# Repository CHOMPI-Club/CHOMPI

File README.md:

# CHOMPI — Open Source

**CHOMPI** is a quirky chromatic sampler and tape-music instrument by
[CHOMPI Club](https://www.chompiclub.com).

This repo contains all of the production files, both hardware and firmware, that make up the CHOMPI Sampler.

---

## What's here

| | |
|---|---|
| [**Firmware — Start Here**](firmware/README.md) | Quick instructions for setting up your development environment, building the firmware, and loading it onto your CHOMPI. |
| [`firmware/chompi-wave`](firmware/chompi-wave/) | **WAVE 1.0**, a wavetable synth firmware that doubles as a starting point for anyone writing their own firmware. |
| [`firmware/chompi-tempo`](firmware/chompi-tempo/) | **TEMPO 1.0**, a pattern generator firmware — the counterpart to TAPE. |
| [`firmware/chompi-tape`](firmware/chompi-tape/) | **TAPE 2.0**, the sampler firmware every CHOMPI ships with. |
| [`firmware/chompi-bootloader-v6.4-beta`](firmware/chompi-bootloader-v6.4-beta/) | This bootloader never shipped on units, but was created to improve stability of the Daisy Seed's integration with CHOMPI's hardware as well as repair edge-case issues related to bugs inherited from older versions of the Electrosmith bootloader.  |
| [`firmware/card-profiles`](firmware/card-profiles/) | The factory microSD card contents for TAPE, TEMPO and WAVE — firmware, samples and settings. |
| [`hardware/hardware-pcb`](hardware/hardware-pcb/) | Schematic, BOM, EAGLE PCB files, and the full fabrication package. |
| [`hardware/hardware-enclosure`](hardware/hardware-enclosure/) | The six pcb panel enclosure files, as well as laser cutting files for diy panels. |

Each folder contains its own README, so check those out for more details.

## What's not here

**The panel artwork.** The graphic set and CHOMPI logos have all been removed for copyright purposes. If you choose to create your own hardware, we ask that you name it something else to avoid trademark infringement.

## Support Guidelines

This is a discontinuation open-source release. As such, this repo is intended to be a permanent source for files and documentation, and will likely not be receiving updates in the future. If you wish to customize your own project, we recommend cloning this repo into your own GitHub.

## Community

Even though this version of CHOMPI is now discontinued, the CLUB is expanding. If you want to discuss this project, share your creations, see what other users have made on their CHOMPI, feel free to check out the CHOMPI Open Source channel on the Chase Bliss Discord.

## License

Everything here is **MIT** — see [`LICENSE`](LICENSE). [`THIRD_PARTY.md`](THIRD_PARTY.md) lists
the work this builds on and the notices that come with it. The CHOMPI name, logo and artwork are
not covered by the license — see [`TRADEMARKS.md`](TRADEMARKS.md).

## HAPPY CHOMPIN'

---

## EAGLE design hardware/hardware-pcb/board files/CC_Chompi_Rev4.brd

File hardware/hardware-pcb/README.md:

# CHOMPI — Hardware, Revision 4

The production files for **CHOMPI**'s two internal circuit boards: schematic, BOM, EAGLE
PCB files, and the full fabrication package that was used by Electro-Smith for manufacturing.

---

## What this is

Two boards, built around the Daisy Seed, laid out as one v-scored panel:

- **Bottom board** — the Daisy Seed2 DFM, a PCM3060 second codec, the MP2722 charger for the
  LiPo battery, USB-C, microSD, MEMS microphone, five 3.5 mm jacks, etc.
- **Top board** — 28 Kailh hot-swap key sockets read through CD4021 shift registers, six
  encoders, 35 addressable RGB LEDs, etc.

1 oz copper, ENIG, black soldermask, SMT assembly on both sides.

## What's in the folder

```
CHOMPI_Rev4_Schematic.pdf     the schematic
CHOMPI_Rev4_BOM.csv           assembly parts list: quantity, manufacturer part number, value,
                              package, designators, etc.
board files/                  the EAGLE project files
  CC_Chompi_Rev4.sch            schematic
  CC_Chompi_Rev4.brd            both boards in one .brd layout
  CC_Chompi_Rev4_1X1.brd        the same boards on the fabrication panel, with rails
fabrication/                  mfg package ordered September 2023
  CC_Chompi_Rev4_1X1.zip        gerbers, drill file, v-score file
  CC_Chompi_Rev4-smd_cleaned_centroid.txt   pick-and-place positions
  CC_Chompi_Rev4_1X1_ordering.txt           the fabrication parameters
```

## What's not here

- **The enclosure.** The six enclosure panels have their own folder.
- **Parts list.** The BOM names a manufacturer part number for every placed part.
- **The rest of the instrument.** The Daisy Seed2 DFM is a separate module; the battery,
  keycaps, knobs and cables aren't included in these files, most of which were custom parts orders.

If you build your own hardware from these files, we ask that you name it something else to
avoid trademark infringement.

## Support Guidelines

This is a discontinuation open-source release. As such, this repo is intended to be a permanent
source for files and documentation, and will likely not be receiving updates in the future. If you wish
to customize your own project, we recommend cloning this repo into your own GitHub.

## Community

Even though this version of CHOMPI is now discontinued, the CLUB is expanding. If you want to
discuss this project, share your creations, see what other users have made on their CHOMPI, feel
free to check out the CHOMPI Open Source channel on the Chase Bliss Discord.

## License

MIT — see [`LICENSE`](../../LICENSE) at the root of this repo. [`THIRD_PARTY.md`](../../THIRD_PARTY.md)
lists the work this builds on. The CHOMPI name and marks are not covered by the license — see
[`TRADEMARKS.md`](../../TRADEMARKS.md).

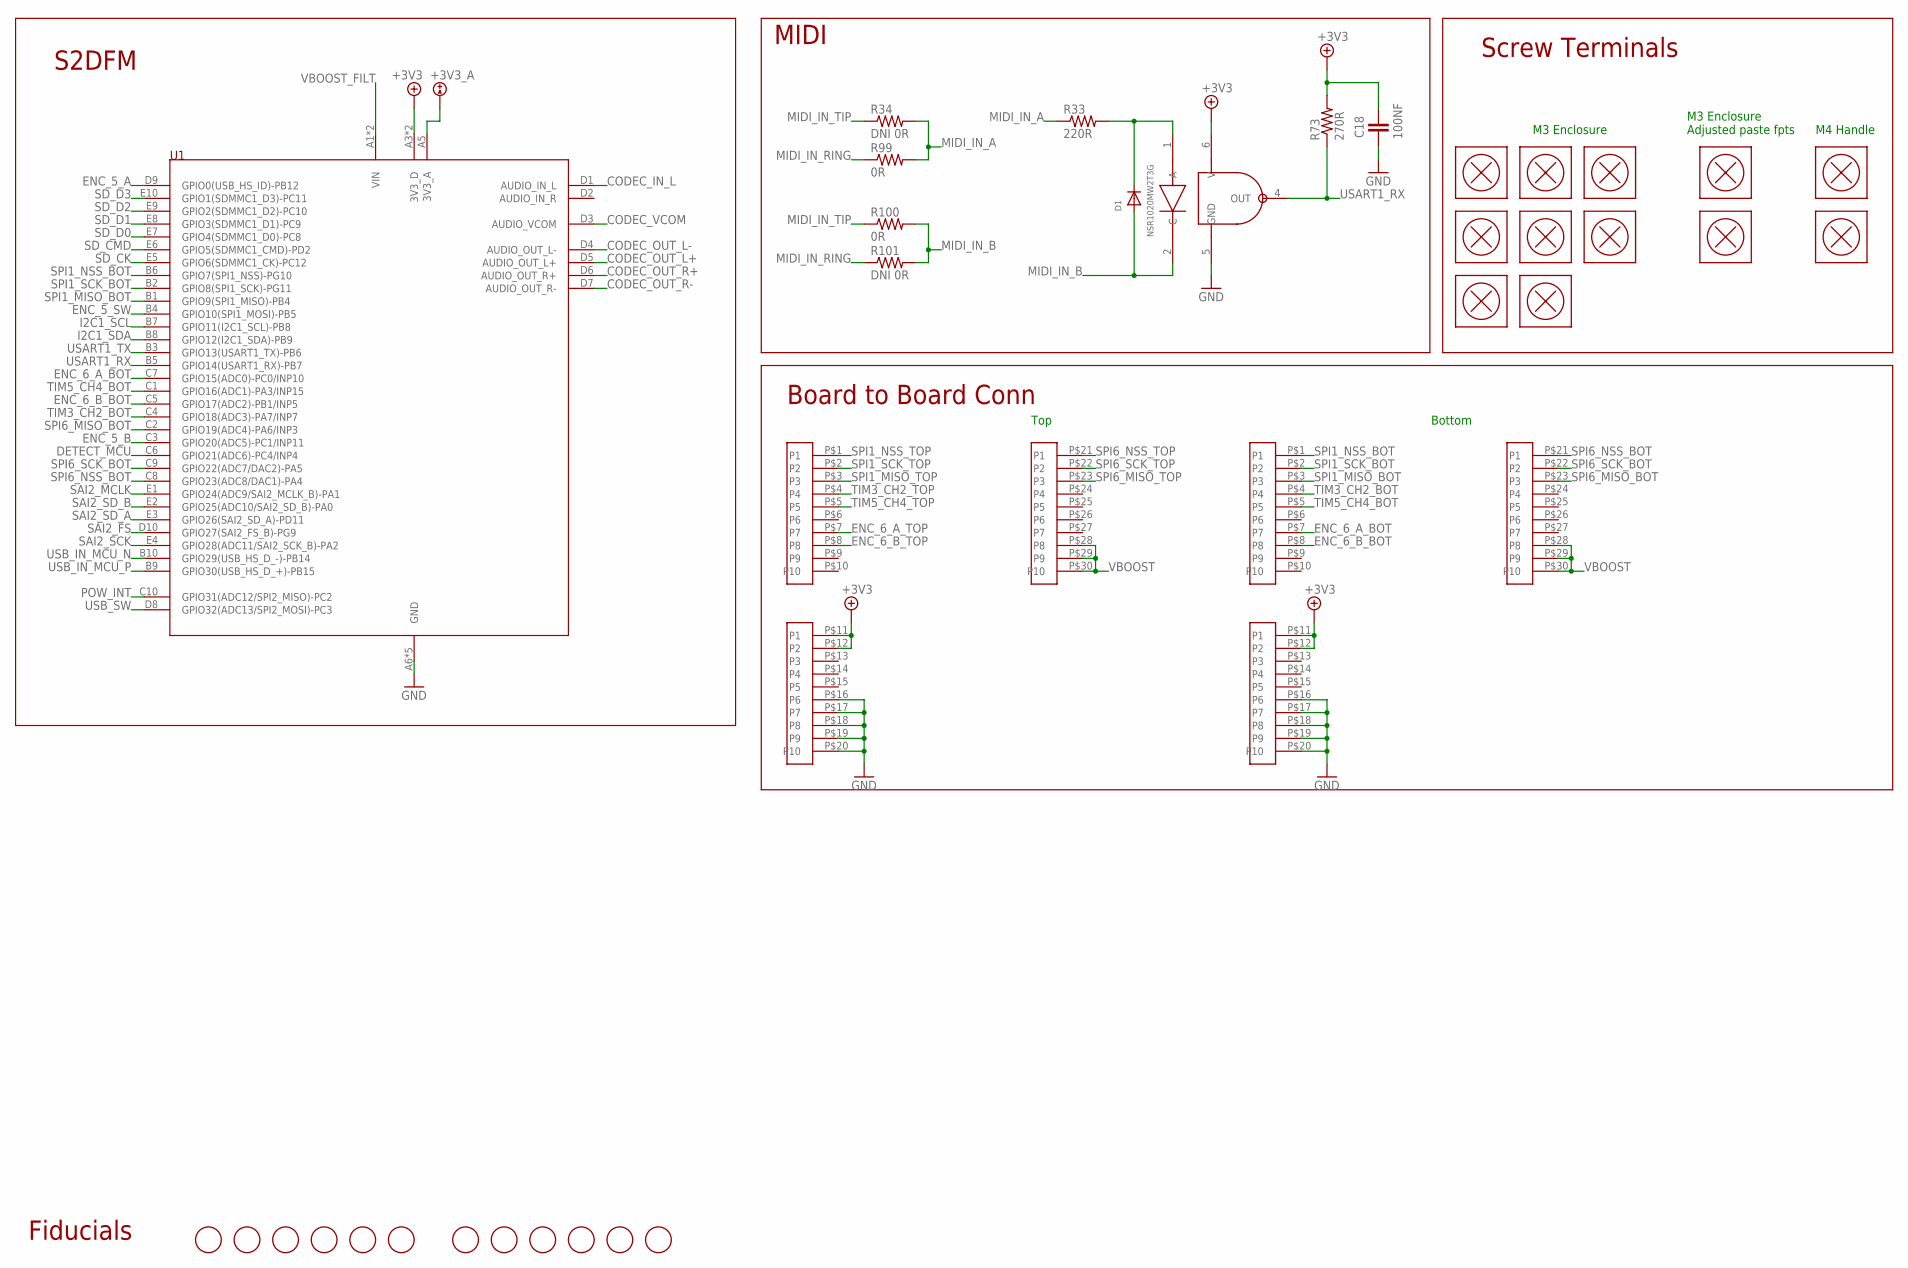
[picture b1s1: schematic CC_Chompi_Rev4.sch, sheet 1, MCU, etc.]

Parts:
C18: 100NF; C0402
D1: NSR1020MW2T3G; SOD-323F
FD1, FD2, FD3, FD4, FD5, FD6, FD7, FD8, FD9, FD10, FD11, FD12: FIDUCIAL; FIDUCIAL_1MM
HANDLE_1, HANDLE_2: SCREW_TERMINALM4; M4_SCREW_TERMINAL
P2, P3: ZIF-30; FH34SRJ-30S-0-5SH-50
R33: 220R; R0603
R34, R101: DNI 0R; R0603
R73: 270R; R0603
R99, R100: 0R; R0603
SCREW_1, SCREW_2, SCREW_3, SCREW_4, SCREW_5, SCREW_7, SCREW_9, SCREW_10: SCREW_TERMINALM3_OLD; T34069_OLD
SCREW_6: SCREW_TERMINALM3_OLD_ADJ2; T34069_OLD_ADJ2
SCREW_8: SCREW_TERMINALM3_OLD_ADJ1; T34069_OLD_ADJ1
U1: ES_DAISY_SEED2_DFM_REV1""; ES_DAISY_SEED2_DFM_REV1
U6: OPTO ISOLATOR; DIL06_GULLWING

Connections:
+3V3: C18.2, P2.P$11 (P1), P2.P$12 (P2), P3.P$11 (P1), P3.P$12 (P2), R73.2, U1.A3 (3V3_D), U1.A4 (3V3_D), U6.6 (V); also elsewhere on the board
+3V3_A: U1.A5 (3V3_A); also elsewhere on the board
CODEC_IN_L: U1.D1 (AUDIO_IN_L); also elsewhere on the board
CODEC_OUT_L+: U1.D5 (AUDIO_OUT_L+); also elsewhere on the board
CODEC_OUT_L-: U1.D4 (AUDIO_OUT_L-); also elsewhere on the board
CODEC_OUT_R+: U1.D6 (AUDIO_OUT_R+); also elsewhere on the board
CODEC_OUT_R-: U1.D7 (AUDIO_OUT_R-); also elsewhere on the board
CODEC_VCOM: U1.D3 (AUDIO_VCOM); also elsewhere on the board
DETECT_MCU: U1.C6 (GPIO21(ADC6)-PC4/INP4); also elsewhere on the board
ENC_5_A: U1.D9 (GPIO0(USB_HS_ID)-PB12); also elsewhere on the board
ENC_5_B: U1.C3 (GPIO20(ADC5)-PC1/INP11); also elsewhere on the board
ENC_5_SW: U1.B4 (GPIO10(SPI1_MOSI)-PB5); also elsewhere on the board
ENC_6_A_BOT: P3.P$7 (P7), U1.C7 (GPIO15(ADC0)-PC0/INP10)
ENC_6_A_TOP: P2.P$7 (P7); also elsewhere on the board
ENC_6_B_BOT: P3.P$8 (P8), U1.C5 (GPIO17(ADC2)-PB1/INP5)
ENC_6_B_TOP: P2.P$8 (P8); also elsewhere on the board
GND: C18.1, P2.P$16 (P6), P2.P$17 (P7), P2.P$18 (P8), P2.P$19 (P9), P2.P$20 (P10), P3.P$16 (P6), P3.P$17 (P7), P3.P$18 (P8), P3.P$19 (P9), P3.P$20 (P10), U1.A6 (GND), U1.A7 (GND), U1.A8 (GND), U1.A9 (GND), U1.A10 (GND), U6.5 (GND); also elsewhere on the board
I2C1_SCL: U1.B7 (GPIO11(I2C1_SCL)-PB8); also elsewhere on the board
I2C1_SDA: U1.B8 (GPIO12(I2C1_SDA)-PB9); also elsewhere on the board
MIDI_IN_A: R33.1, R34.2, R99.2
MIDI_IN_B: D1.A, R100.2, R101.2, U6.2 (C)
MIDI_IN_RING: R99.1, R101.1; also elsewhere on the board
MIDI_IN_TIP: R34.1, R100.1; also elsewhere on the board
unnamed: D1.C, R33.2, U6.1 (A)
POW_INT: U1.C10 (GPIO31(ADC12/SPI2_MISO)-PC2); also elsewhere on the board
SAI2_FS: U1.D10 (GPIO27(SAI2_FS_B)-PG9); also elsewhere on the board
SAI2_MCLK: U1.E1 (GPIO24(ADC9/SAI2_MCLK_B)-PA1); also elsewhere on the board
SAI2_SCK: U1.E4 (GPIO28(ADC11/SAI2_SCK_B)-PA2); also elsewhere on the board
SAI2_SD_A: U1.E3 (GPIO26(SAI2_SD_A)-PD11); also elsewhere on the board
SAI2_SD_B: U1.E2 (GPIO25(ADC10/SAI2_SD_B)-PA0); also elsewhere on the board
SD_CK: U1.E5 (GPIO6(SDMMC1_CK)-PC12); also elsewhere on the board
SD_CMD: U1.E6 (GPIO5(SDMMC1_CMD)-PD2); also elsewhere on the board
SD_D0: U1.E7 (GPIO4(SDMMC1_D0)-PC8); also elsewhere on the board
SD_D1: U1.E8 (GPIO3(SDMMC1_D1)-PC9); also elsewhere on the board
SD_D2: U1.E9 (GPIO2(SDMMC1_D2)-PC10); also elsewhere on the board
SD_D3: U1.E10 (GPIO1(SDMMC1_D3)-PC11); also elsewhere on the board
SPI1_MISO_BOT: P3.P$3 (P3), U1.B1 (GPIO9(SPI1_MISO)-PB4)
SPI1_MISO_TOP: P2.P$3 (P3); also elsewhere on the board
SPI1_NSS_BOT: P3.P$1 (P1), U1.B6 (GPIO7(SPI1_NSS)-PG10)
SPI1_NSS_TOP: P2.P$1 (P1); also elsewhere on the board
SPI1_SCK_BOT: P3.P$2 (P2), U1.B2 (GPIO8(SPI1_SCK)-PG11)
SPI1_SCK_TOP: P2.P$2 (P2); also elsewhere on the board
SPI6_MISO_BOT: P3.P$23 (P3), U1.C2 (GPIO19(ADC4)-PA6/INP3)
SPI6_MISO_TOP: P2.P$23 (P3); also elsewhere on the board
SPI6_NSS_BOT: P3.P$21 (P1), U1.C8 (GPIO23(ADC8/DAC1)-PA4)
SPI6_NSS_TOP: P2.P$21 (P1); also elsewhere on the board
SPI6_SCK_BOT: P3.P$22 (P2), U1.C9 (GPIO22(ADC7/DAC2)-PA5)
SPI6_SCK_TOP: P2.P$22 (P2); also elsewhere on the board
TIM3_CH2_BOT: P3.P$4 (P4), U1.C4 (GPIO18(ADC3)-PA7/INP7)
TIM3_CH2_TOP: P2.P$4 (P4); also elsewhere on the board
TIM5_CH4_BOT: P3.P$5 (P5), U1.C1 (GPIO16(ADC1)-PA3/INP15)
TIM5_CH4_TOP: P2.P$5 (P5); also elsewhere on the board
USART1_RX: R73.1, U1.B5 (GPIO14(USART1_RX)-PB7), U6.4 (OUT)
USART1_TX: U1.B3 (GPIO13(USART1_TX)-PB6); also elsewhere on the board
USB_IN_MCU_N: U1.B10 (GPIO29(USB_HS_D_-)-PB14); also elsewhere on the board
USB_IN_MCU_P: U1.B9 (GPIO30(USB_HS_D_+)-PB15); also elsewhere on the board
USB_SW: U1.D8 (GPIO32(ADC13/SPI2_MOSI)-PC3); also elsewhere on the board
VBOOST: P2.P$28 (P8), P2.P$29 (P9), P2.P$30 (P10), P3.P$28 (P8), P3.P$29 (P9), P3.P$30 (P10); also elsewhere on the board
VBOOST_FILT: U1.A1 (VIN), U1.A2 (VIN); also elsewhere on the board

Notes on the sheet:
MIDI
S2DFM
Top
Bottom
M3 Enclosure
M4 Handle
Board to Board Conn
Screw Terminals
Fiducials
M3 Enclosure Adjusted paste fpts

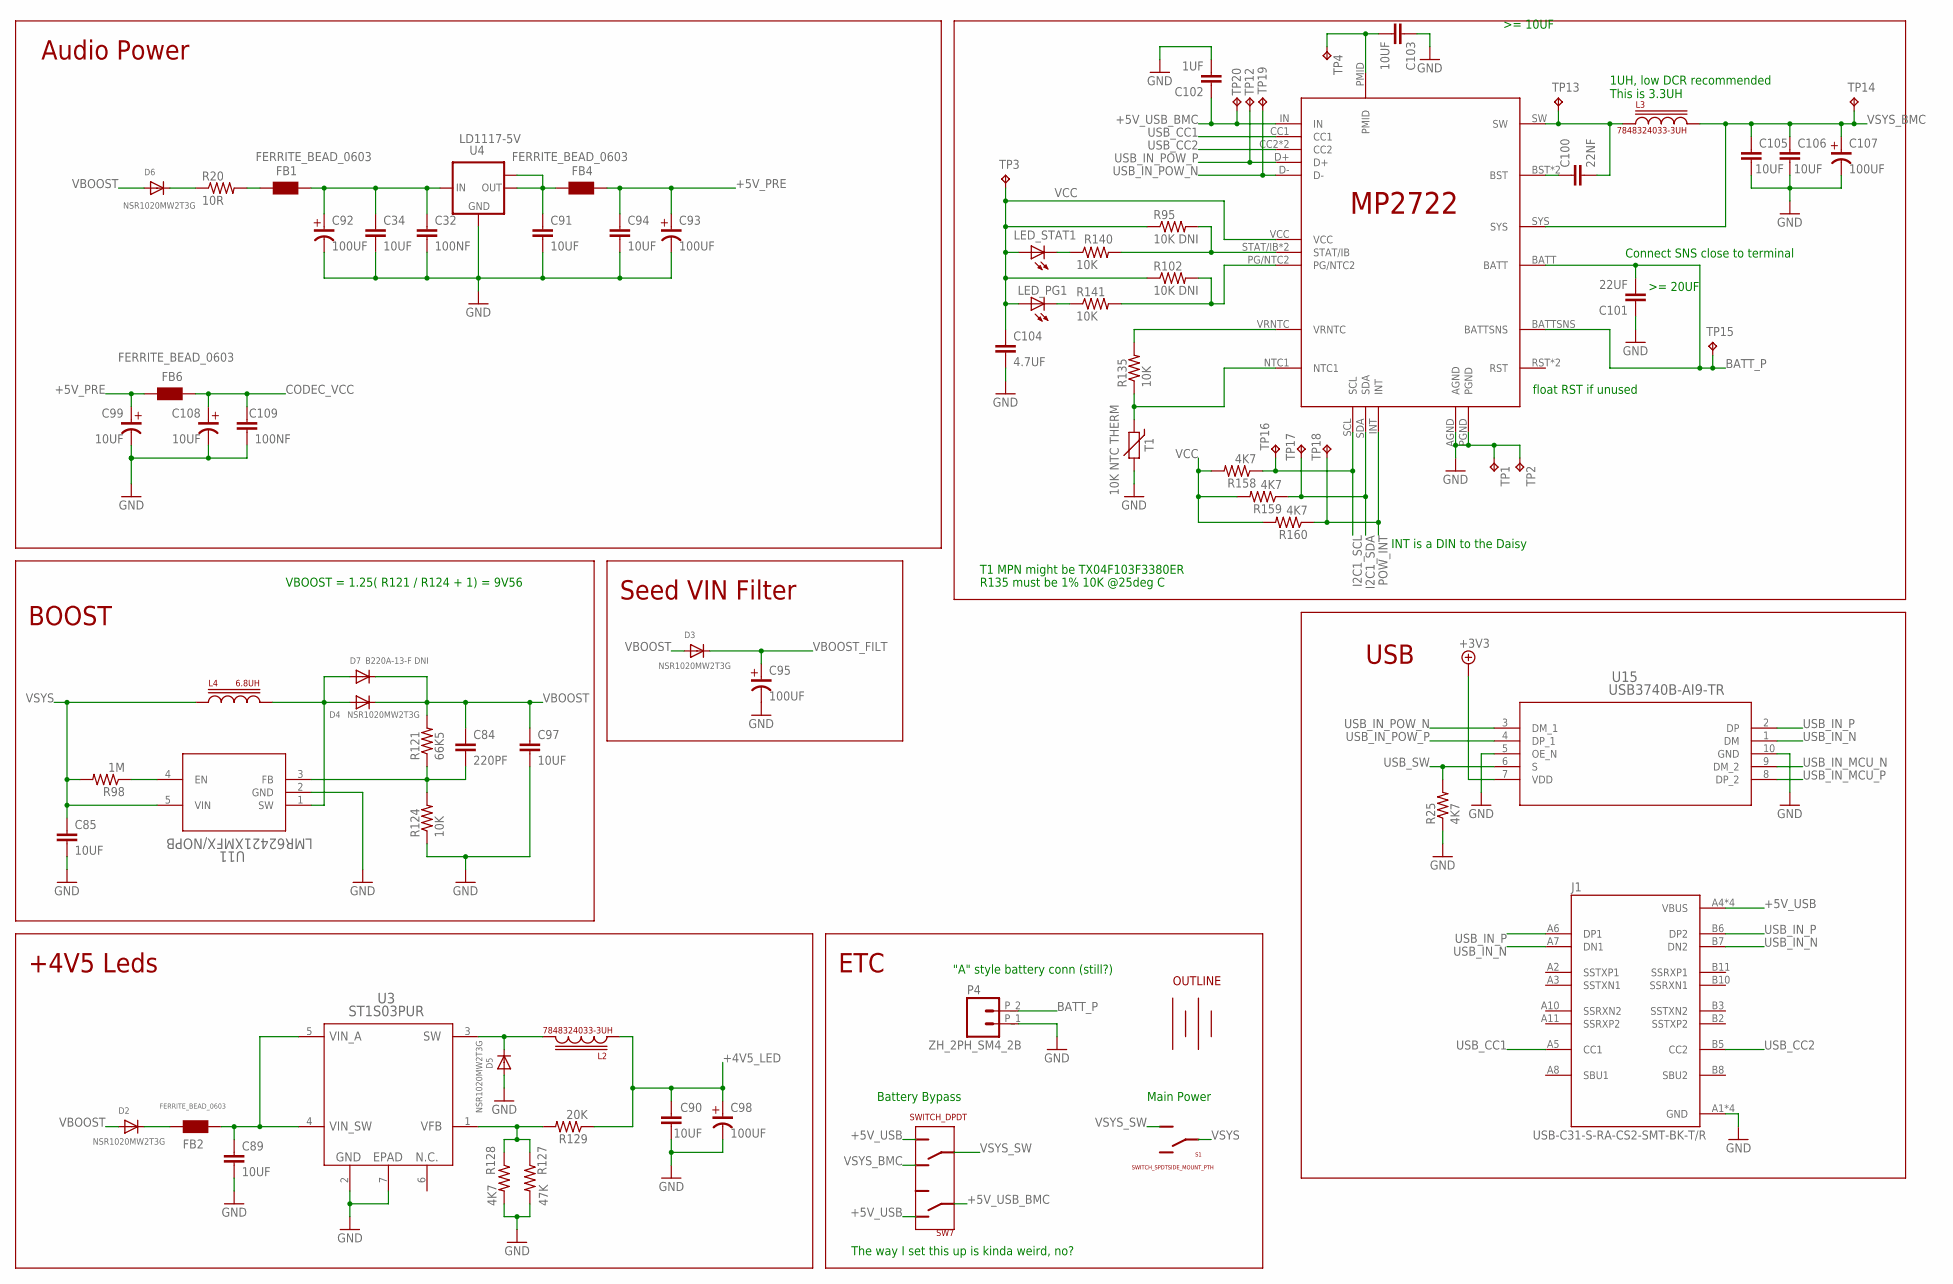
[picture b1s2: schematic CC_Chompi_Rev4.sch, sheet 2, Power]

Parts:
C32, C109: 100NF; C0402
C34, C85, C89, C90, C91, C94, C97, C103, C105, C106: 10UF; C0805
C84: 220PF; C0603
C92, C93, C95, C98, C107: 100UF; PANASONIC_D
C99, C108: 10UF; PANASONIC_B
C100: 22NF; C0603
C101: 22UF; C1206
C102: 1UF; C0603
C104: 4.7UF; C0603
D2, D3, D4, D5, D6: NSR1020MW2T3G; SOD-323F
D7: B220A-13-F DNI; SMADIODE
FB1, FB2, FB4, FB6: FERRITE_BEAD_0603; WUERTH-ELEKTRONIK_0603
J1: USB-C31-S-RA-CS2-SMT-BK-T/R; ADAM_USB-C31-S-RA-CS2-SMT-BK-T/R
L2, L3: 7848324033-3UH; I1008
L4: 6.8UH; MPL-SE6040
LED_PG1: LED_RED_0603; DIODE_0603
LED_STAT1: LED_RED_0603; DIODE_0603
P4: ZH_2PH_SM4_2B; S2B-PH-SM4-TB(LF)(SN)
R20: 10R; R0603
R25, R128, R158, R159, R160: 4K7; R0603
R95, R102: 10K DNI; R0603
R98: 1M; R0603
R121: 66K5; R0603
R124, R135, R140, R141: 10K; R0603
R127: 47K; R0603
R129: 20K; R0603
S1: SWITCH_SPDTSIDE_MOUNT_PTH; SK-12F17-G7
SW7: SWITCH_DPDT; MSS6-V-T/R
T1: 10K NTC THERM; R0603
TP1, TP2, TP3, TP12, TP13, TP14, TP15, TP16, TP17, TP18, TP19, TP20: TPTP20R; TP20R
TP4: TPTP13R; TP13R
U3: ST1S03PUR; DFN06_3X3_STM
U4: LD1117-5V; SOT223
U11: LMR62421XMFX/NOPB; MF05A
U13: MP2722 Buck Charger; MP2722
U15: USB3740B-AI9-TR; QFN10_1P6X2P1MC_MCH
U$1: LP346384

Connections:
+3V3: U15.7 (VDD); also elsewhere on the board
+4V5_LED: C90.1, C98.+ (POS), L2.2, R129.1; also elsewhere on the board
+5V_PRE: C93.+ (POS), C94.1, C99.+ (POS), FB4.2, FB6.2
+5V_USB: J1.A4 (VBUS), J1.A9 (VBUS), J1.B4 (VBUS), J1.B9 (VBUS), SW7.A (T1.1), SW7.F (T2.2)
+5V_USB_BMC: C102.1, SW7.B (P1), TP20.TP, U13.IN
BATT_P: C101.2, P4.P_2 (3), TP15.TP, U13.BATT, U13.BATTSNS
BATT_THERM: R135.1, T1.1, U13.NTC1
CODEC_VCC: C108.+ (POS), C109.1, FB6.1; also elsewhere on the board
GND: C32.2, C34.2, C85.2, C89.2, C90.2, C91.2, C92.- (NEG), C93.- (NEG), C94.2, C95.- (NEG), C97.2, C98.- (NEG), C99.- (NEG), C101.1, C102.2, C103.1, C104.2, C105.2, C106.2, C107.- (NEG), C108.- (NEG), C109.2, D5.A, J1.A1 (GND), J1.A12 (GND), J1.B1 (GND), J1.B12 (GND), P4.P_1 (2), R25.1, R124.1, R127.2, R128.2, T1.2, TP1.TP, TP2.TP, U3.2 (GND), U3.7 (EPAD), U4.1 (GND), U11.2 (GND), U13.AGND, U13.PGND, U15.5 (OE_N), U15.10 (GND); also elsewhere on the board
I2C1_SCL: R158.1, TP16.TP, U13.SCL; also elsewhere on the board
I2C1_SDA: R159.1, TP17.TP, U13.SDA; also elsewhere on the board
unnamed: C100.1, U13.BST, U13.BST_2 (BST)
unnamed: D2.C, FB2.1
unnamed: R135.2, U13.VRNTC
unnamed: FB1.1, R20.2
unnamed: D6.C, R20.1
unnamed: C32.1, C34.1, C92.+ (POS), FB1.2, U4.3 (IN)
unnamed: C84.2, R121.1, R124.2, U11.3 (FB)
unnamed: LED_STAT1.CATHODE (C), R140.1
unnamed: LED_PG1.CATHODE (C), R141.1
unnamed: D4.A, D7.A, L4.P$2, U11.1 (SW)
unnamed: C89.1, FB2.2, U3.4 (VIN_SW), U3.5 (VIN_A)
unnamed: R127.1, R128.1, R129.2, U3.1 (VFB)
unnamed: D5.C, L2.1, U3.3 (SW)
unnamed: R98.1, U11.4 (EN)
PG: R102.2, R141.2, U13.PG/NTC2
PMID: C103.2, TP4.TP, U13.PMID
POW_INT: R160.1, TP18.TP, U13.INT; also elsewhere on the board
STAT: R95.2, R140.2, U13.STAT/IB, U13.STAT/IB_2 (STAT/IB)
SW: C100.2, L3.2, TP13.TP, U13.SW
USB_CC1: J1.A5 (CC1), U13.CC1
USB_CC2: J1.B5 (CC2), U13.CC2, U13.CC2_2 (CC2)
USB_IN_MCU_N: U15.9 (DM_2); also elsewhere on the board
USB_IN_MCU_P: U15.8 (DP_2); also elsewhere on the board
USB_IN_N: J1.A7 (DN1), J1.B7 (DN2), U15.1 (DM)
USB_IN_P: J1.A6 (DP1), J1.B6 (DP2), U15.2 (DP)
USB_IN_POW_N: TP19.TP, U13.D-, U15.3 (DM_1)
USB_IN_POW_P: TP12.TP, U13.D+, U15.4 (DP_1)
USB_SW: R25.2, U15.6 (S); also elsewhere on the board
VBOOST: C84.1, C97.1, D2.A, D3.A, D4.C, D6.A, D7.C, R121.2; also elsewhere on the board
VBOOST_FILT: C95.+ (POS), D3.C; also elsewhere on the board
VCC: C104.1, LED_PG1.ANODE (A), LED_STAT1.ANODE (A), R95.1, R102.1, R158.2, R159.2, R160.2, TP3.TP, U13.VCC
VSYS: C85.1, L4.P$1, R98.2, S1.P$1, U11.5 (VIN)
VSYS_BMC: C105.1, C106.1, C107.+ (POS), L3.1, SW7.D (T2.1), TP14.TP, U13.SYS
VSYS_SW: S1.P$2 (T0), SW7.E (P2)
V_REG_2: C91.1, FB4.1, U4.2 (OUT), U4.TAB (OUT1)

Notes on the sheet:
BOOST
VBOOST = 1.25( R121 / R124 + 1) = 9V56
+4V5 Leds
1UH, low DCR recommended This is 3.3UH
INT is a DIN to the Daisy
float RST if unused
Connect SNS close to terminal
"A" style battery conn (still?)
USB
ETC
Seed VIN Filter
Audio Power
T1 MPN might be TX04F103F3380ER
R135 must be 1% 10K @25deg C
The way I set this up is kinda weird, no?
Battery Bypass
Main Power

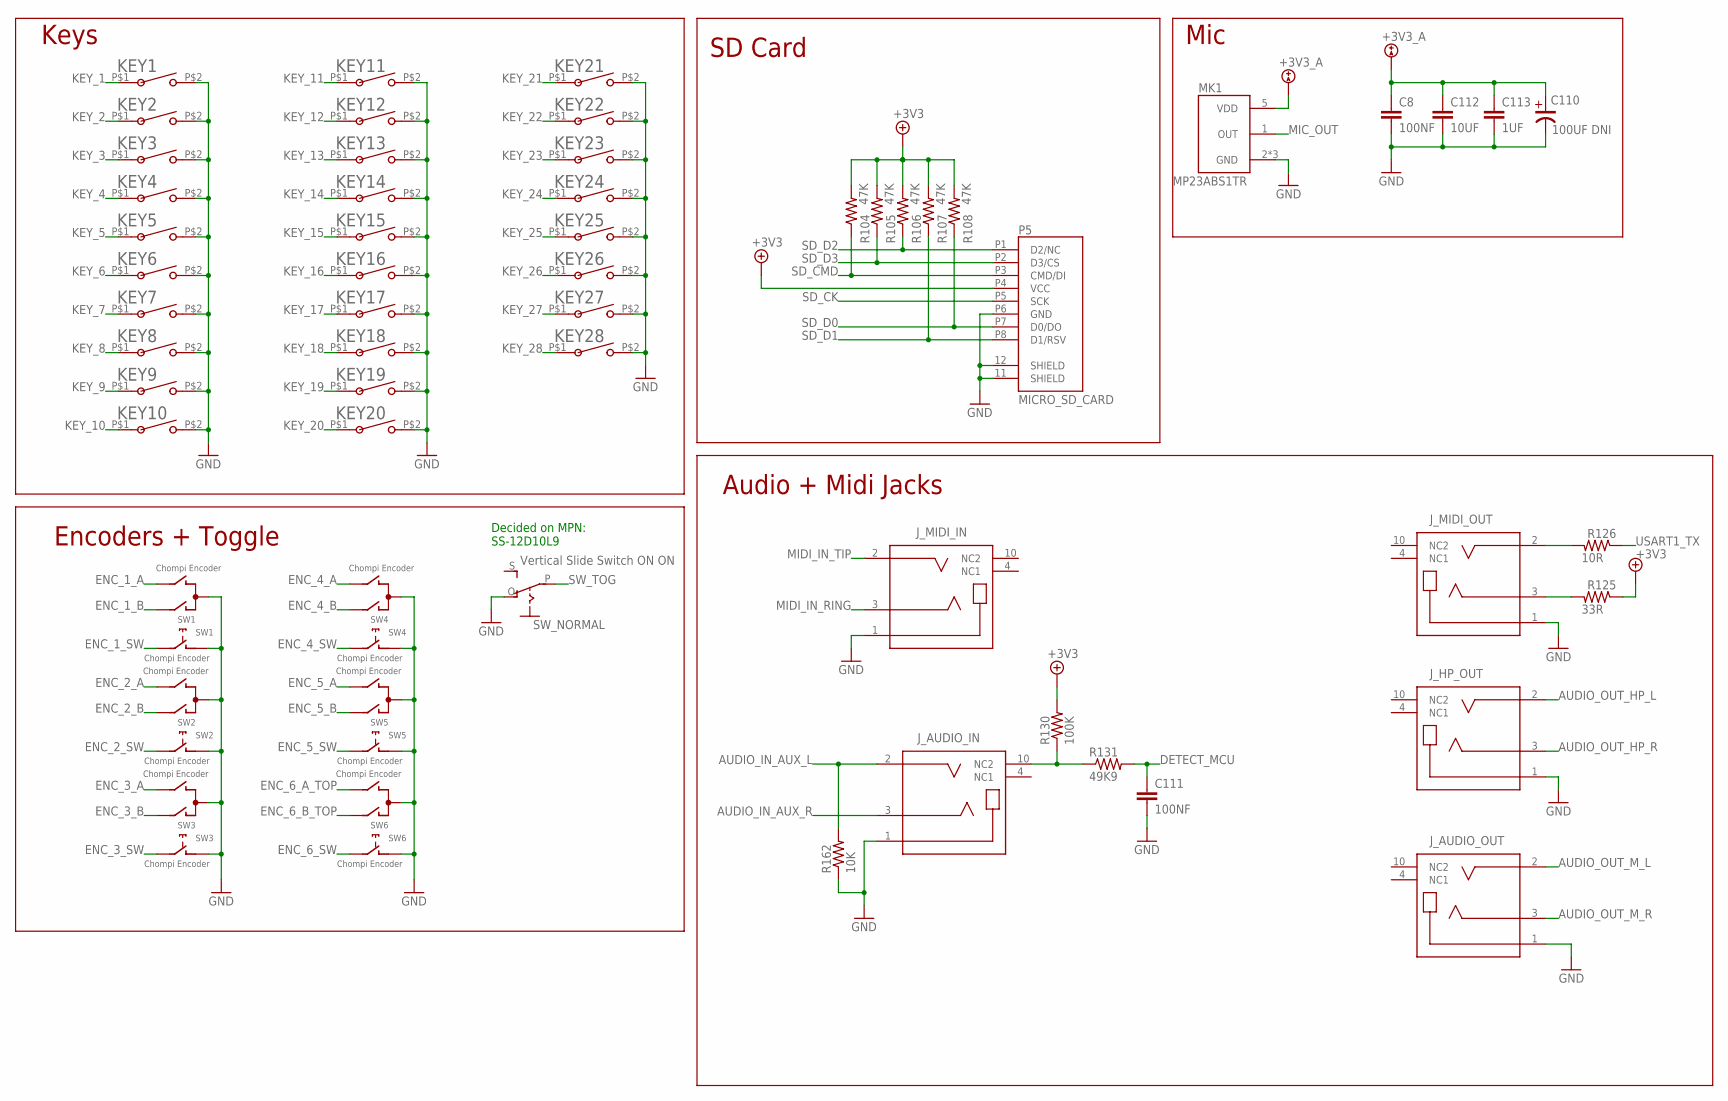
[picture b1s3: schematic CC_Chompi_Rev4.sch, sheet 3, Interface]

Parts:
C8, C111: 100NF; C0402
C110: 100UF DNI; PANASONIC_D
C112: 10UF; C0805
C113: 1UF; C0603
J_AUDIO_IN: PJ-3062-HD-R; CUI_SJ2-35863B1-SMT-TR
J_AUDIO_OUT: PJ-3062-HD-B; CUI_SJ2-35863B1-SMT-TR
J_HP_OUT: PJ-3062-G; CUI_SJ2-35863B1-SMT-TR
J_MIDI_IN: PJ-3062-HD-B; CUI_SJ2-35863B1-SMT-TR
J_MIDI_OUT: PJ-3062-HD-B; CUI_SJ2-35863B1-SMT-TR
KEY1, KEY2, KEY3, KEY4, KEY5, KEY6, KEY7, KEY8, KEY9, KEY10, KEY11, KEY12, KEY13, KEY14, KEY15, KEY16, KEY17, KEY18, KEY19, KEY20, KEY21, KEY22, KEY23, KEY24, KEY25, KEY26, KEY27, KEY28: MX3A-L1NB_SOCKET; CPG151101S11
MK1: MP23ABS1TR; MIC_MP23ABS1TR
P5: MICRO_SD_CARD; MEM2061-01-188-00-A_GCT
R104, R105, R106, R107, R108: 47K; R0603
R125: 33R; R0603
R126: 10R; R0603
R130: 100K; R0402
R131: 49K9; R0603
R162: 10K; R0603
SW1, SW2, SW3, SW4, SW5, SW6: Chompi Encoder; PEC11_SILK
SW_NORMAL: Vertical Slide Switch ON ON; ES_100SP1T6B11M2QEH_SMALL

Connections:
+3V3: P5.P4 (VCC), R104.2, R105.2, R106.2, R107.2, R108.2, R125.1, R130.2; also elsewhere on the board
+3V3_A: C8.1, C110.+ (POS), C112.1, C113.1, MK1.5 (VDD); also elsewhere on the board
AUDIO_IN_AUX_L: J_AUDIO_IN.2 (TIP), R162.2; also elsewhere on the board
AUDIO_IN_AUX_R: J_AUDIO_IN.3 (RING); also elsewhere on the board
AUDIO_OUT_HP_L: J_HP_OUT.2 (TIP); also elsewhere on the board
AUDIO_OUT_HP_R: J_HP_OUT.3 (RING); also elsewhere on the board
AUDIO_OUT_M_L: J_AUDIO_OUT.2 (TIP); also elsewhere on the board
AUDIO_OUT_M_R: J_AUDIO_OUT.3 (RING); also elsewhere on the board
DETECT: J_AUDIO_IN.10 (NC2), R130.1, R131.1
DETECT_MCU: C111.1, R131.2; also elsewhere on the board
ENC_1_A: SW1.B; also elsewhere on the board
ENC_1_B: SW1.A; also elsewhere on the board
ENC_1_SW: SW1.E (2); also elsewhere on the board
ENC_2_A: SW2.B; also elsewhere on the board
ENC_2_B: SW2.A; also elsewhere on the board
ENC_2_SW: SW2.E (2); also elsewhere on the board
ENC_3_A: SW3.B; also elsewhere on the board
ENC_3_B: SW3.A; also elsewhere on the board
ENC_3_SW: SW3.E (2); also elsewhere on the board
ENC_4_A: SW4.B; also elsewhere on the board
ENC_4_B: SW4.A; also elsewhere on the board
ENC_4_SW: SW4.E (2); also elsewhere on the board
ENC_5_A: SW5.B; also elsewhere on the board
ENC_5_B: SW5.A; also elsewhere on the board
ENC_5_SW: SW5.E (2); also elsewhere on the board
ENC_6_A_TOP: SW6.B; also elsewhere on the board
ENC_6_B_TOP: SW6.A; also elsewhere on the board
ENC_6_SW: SW6.E (2); also elsewhere on the board
GND: C8.2, C110.- (NEG), C111.2, C112.2, C113.2, J_AUDIO_IN.1 (SLEEVE), J_AUDIO_OUT.1 (SLEEVE), J_HP_OUT.1 (SLEEVE), J_MIDI_IN.1 (SLEEVE), J_MIDI_OUT.1 (SLEEVE), KEY1.P$2 (2), KEY2.P$2 (2), KEY3.P$2 (2), KEY4.P$2 (2), KEY5.P$2 (2), KEY6.P$2 (2), KEY7.P$2 (2), KEY8.P$2 (2), KEY9.P$2 (2), KEY10.P$2 (2), KEY11.P$2 (2), KEY12.P$2 (2), KEY13.P$2 (2), KEY14.P$2 (2), KEY15.P$2 (2), KEY16.P$2 (2), KEY17.P$2 (2), KEY18.P$2 (2), KEY19.P$2 (2), KEY20.P$2 (2), KEY21.P$2 (2), KEY22.P$2 (2), KEY23.P$2 (2), KEY24.P$2 (2), KEY25.P$2 (2), KEY26.P$2 (2), KEY27.P$2 (2), KEY28.P$2 (2), MK1.2 (GND), MK1.3 (GND), MK1.4 (GND), P5.11 (SHIELD), P5.12 (SHIELD), P5.P6 (GND), R162.1, SW1.C, SW1.D (1), SW2.C, SW2.D (1), SW3.C, SW3.D (1), SW4.C, SW4.D (1), SW5.C, SW5.D (1), SW6.C, SW6.D (1), SW_NORMAL.O; also elsewhere on the board
KEY_1: KEY1.P$1 (1); also elsewhere on the board
KEY_2: KEY2.P$1 (1); also elsewhere on the board
KEY_3: KEY3.P$1 (1); also elsewhere on the board
KEY_4: KEY4.P$1 (1); also elsewhere on the board
KEY_5: KEY5.P$1 (1); also elsewhere on the board
KEY_6: KEY6.P$1 (1); also elsewhere on the board
KEY_7: KEY7.P$1 (1); also elsewhere on the board
KEY_8: KEY8.P$1 (1); also elsewhere on the board
KEY_9: KEY9.P$1 (1); also elsewhere on the board
KEY_10: KEY10.P$1 (1); also elsewhere on the board
KEY_11: KEY11.P$1 (1); also elsewhere on the board
KEY_12: KEY12.P$1 (1); also elsewhere on the board
KEY_13: KEY13.P$1 (1); also elsewhere on the board
KEY_14: KEY14.P$1 (1); also elsewhere on the board
KEY_15: KEY15.P$1 (1); also elsewhere on the board
KEY_16: KEY16.P$1 (1); also elsewhere on the board
KEY_17: KEY17.P$1 (1); also elsewhere on the board
KEY_18: KEY18.P$1 (1); also elsewhere on the board
KEY_19: KEY19.P$1 (1); also elsewhere on the board
KEY_20: KEY20.P$1 (1); also elsewhere on the board
KEY_21: KEY21.P$1 (1); also elsewhere on the board
KEY_22: KEY22.P$1 (1); also elsewhere on the board
KEY_23: KEY23.P$1 (1); also elsewhere on the board
KEY_24: KEY24.P$1 (1); also elsewhere on the board
KEY_25: KEY25.P$1 (1); also elsewhere on the board
KEY_26: KEY26.P$1 (1); also elsewhere on the board
KEY_27: KEY27.P$1 (1); also elsewhere on the board
KEY_28: KEY28.P$1 (1); also elsewhere on the board
MIC_OUT: MK1.1 (OUT); also elsewhere on the board
MIDI_IN_RING: J_MIDI_IN.3 (RING); also elsewhere on the board
MIDI_IN_TIP: J_MIDI_IN.2 (TIP); also elsewhere on the board
unnamed: J_MIDI_OUT.3 (RING), R125.2
unnamed: J_MIDI_OUT.2 (TIP), R126.2
SD_CK: P5.P5 (SCK); also elsewhere on the board
SD_CMD: P5.P3 (CMD/DI), R104.1; also elsewhere on the board
SD_D0: P5.P7 (D0/DO), R108.1; also elsewhere on the board
SD_D1: P5.P8 (D1/RSV), R107.1; also elsewhere on the board
SD_D2: P5.P1 (D2/NC), R106.1; also elsewhere on the board
SD_D3: P5.P2 (D3/CS), R105.1; also elsewhere on the board
SW_TOG: SW_NORMAL.P; also elsewhere on the board
USART1_TX: R126.1; also elsewhere on the board

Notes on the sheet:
Keys
Encoders + Toggle
SD Card
Audio + Midi Jacks
Mic
Decided on MPN: SS-12D10L9

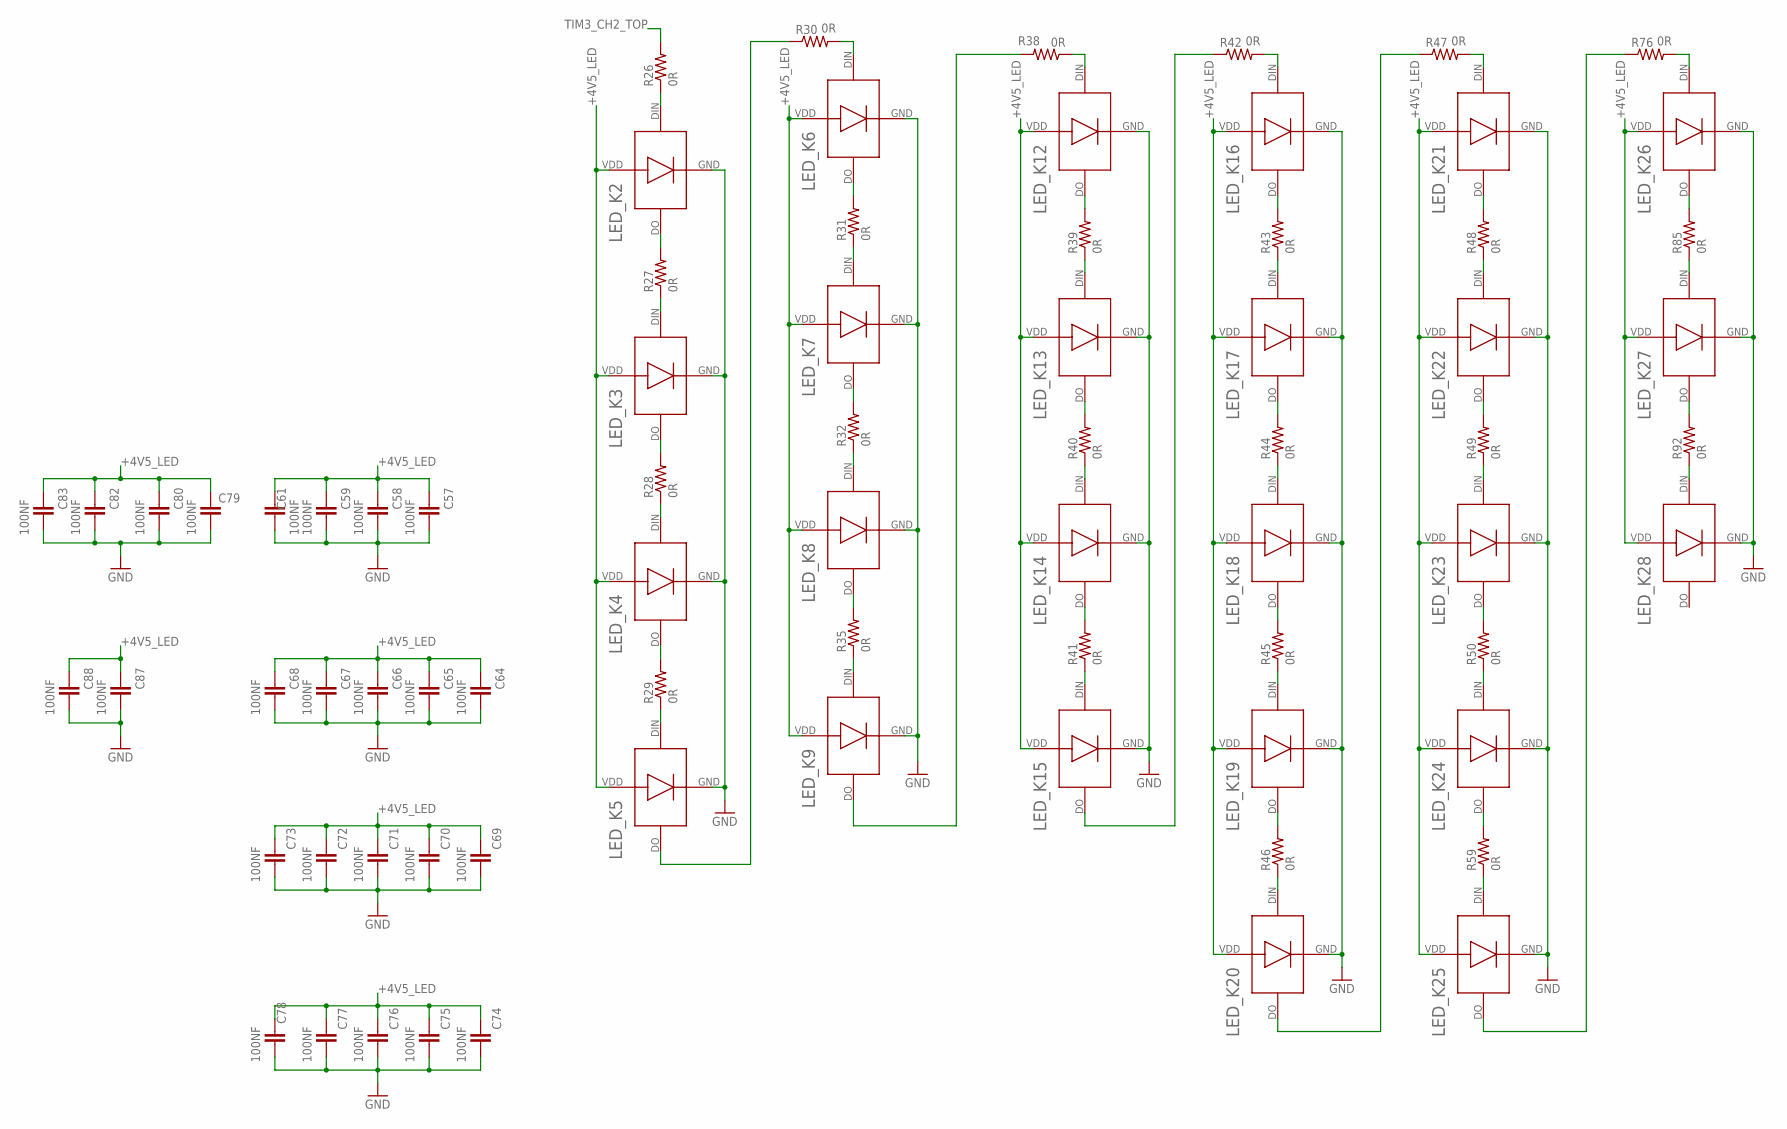
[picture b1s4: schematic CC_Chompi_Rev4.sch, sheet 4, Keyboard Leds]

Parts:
C57, C58, C59, C61, C64, C65, C66, C67, C68, C69, C70, C71, C72, C73, C74, C75, C76, C77, C78, C79, C80, C82, C83, C87, C88: 100NF; C0402
LED_K2, LED_K3, LED_K4, LED_K5, LED_K6, LED_K7, LED_K8, LED_K9, LED_K12, LED_K13, LED_K14, LED_K15, LED_K16, LED_K17, LED_K18, LED_K19, LED_K20, LED_K21, LED_K22, LED_K23, LED_K24, LED_K25, LED_K26, LED_K27, LED_K28: Digital LED Reverse Mount; IN-PI32TAR
R26, R27, R28, R29, R30, R31, R32, R35, R38, R39, R40, R41, R42, R43, R44, R45, R46, R47, R48, R49, R50, R59, R76, R85, R92: 0R; R0603

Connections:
+4V5_LED: C57.1, C58.1, C59.1, C61.1, C64.1, C65.1, C66.1, C67.1, C68.1, C69.1, C70.1, C71.1, C72.1, C73.1, C74.1, C75.1, C76.1, C77.1, C78.1, C79.1, C80.1, C82.1, C83.1, C87.1, C88.1, LED_K2.VDD, LED_K3.VDD, LED_K4.VDD, LED_K5.VDD, LED_K6.VDD, LED_K7.VDD, LED_K8.VDD, LED_K9.VDD, LED_K12.VDD, LED_K13.VDD, LED_K14.VDD, LED_K15.VDD, LED_K16.VDD, LED_K17.VDD, LED_K18.VDD, LED_K19.VDD, LED_K20.VDD, LED_K21.VDD, LED_K22.VDD, LED_K23.VDD, LED_K24.VDD, LED_K25.VDD, LED_K26.VDD, LED_K27.VDD, LED_K28.VDD; also elsewhere on the board
GND: C57.2, C58.2, C59.2, C61.2, C64.2, C65.2, C66.2, C67.2, C68.2, C69.2, C70.2, C71.2, C72.2, C73.2, C74.2, C75.2, C76.2, C77.2, C78.2, C79.2, C80.2, C82.2, C83.2, C87.2, C88.2, LED_K2.GND (VSS), LED_K3.GND (VSS), LED_K4.GND (VSS), LED_K5.GND (VSS), LED_K6.GND (VSS), LED_K7.GND (VSS), LED_K8.GND (VSS), LED_K9.GND (VSS), LED_K12.GND (VSS), LED_K13.GND (VSS), LED_K14.GND (VSS), LED_K15.GND (VSS), LED_K16.GND (VSS), LED_K17.GND (VSS), LED_K18.GND (VSS), LED_K19.GND (VSS), LED_K20.GND (VSS), LED_K21.GND (VSS), LED_K22.GND (VSS), LED_K23.GND (VSS), LED_K24.GND (VSS), LED_K25.GND (VSS), LED_K26.GND (VSS), LED_K27.GND (VSS), LED_K28.GND (VSS); also elsewhere on the board
unnamed: LED_K5.DO, R30.1
unnamed: LED_K2.DIN (DI), R26.1
unnamed: LED_K2.DO, R27.2
unnamed: LED_K3.DIN (DI), R27.1
unnamed: LED_K3.DO, R28.2
unnamed: LED_K4.DIN (DI), R28.1
unnamed: LED_K4.DO, R29.2
unnamed: LED_K5.DIN (DI), R29.1
unnamed: LED_K13.DIN (DI), R39.1
unnamed: LED_K6.DIN (DI), R30.2
unnamed: LED_K6.DO, R31.2
unnamed: LED_K7.DIN (DI), R31.1
unnamed: LED_K7.DO, R32.2
unnamed: LED_K14.DIN (DI), R40.1
unnamed: LED_K18.DIN (DI), R44.1
unnamed: LED_K19.DIN (DI), R45.1
unnamed: LED_K23.DIN (DI), R49.1
unnamed: LED_K24.DIN (DI), R50.1
unnamed: LED_K13.DO, R40.2
unnamed: LED_K15.DO, R42.1
unnamed: LED_K12.DIN (DI), R38.1
unnamed: LED_K12.DO, R39.2
unnamed: LED_K14.DO, R41.2
unnamed: LED_K18.DO, R45.2
unnamed: LED_K19.DO, R46.2
unnamed: LED_K23.DO, R50.2
unnamed: LED_K24.DO, R59.2
unnamed: LED_K15.DIN (DI), R41.1
unnamed: LED_K20.DO, R47.1
unnamed: LED_K16.DIN (DI), R42.2
unnamed: LED_K16.DO, R43.2
unnamed: LED_K17.DIN (DI), R43.1
unnamed: LED_K17.DO, R44.2
unnamed: LED_K20.DIN (DI), R46.1
unnamed: LED_K25.DIN (DI), R59.1
unnamed: LED_K9.DO, R38.2
unnamed: LED_K8.DIN (DI), R32.1
unnamed: LED_K9.DIN (DI), R35.1
unnamed: LED_K25.DO, R76.1
unnamed: LED_K21.DIN (DI), R47.2
unnamed: LED_K21.DO, R48.2
unnamed: LED_K22.DIN (DI), R48.1
unnamed: LED_K22.DO, R49.2
unnamed: LED_K8.DO, R35.2
unnamed: LED_K26.DIN (DI), R76.2
unnamed: LED_K26.DO, R85.2
unnamed: LED_K27.DIN (DI), R85.1
unnamed: LED_K27.DO, R92.2
unnamed: LED_K28.DIN (DI), R92.1
TIM3_CH2_TOP: R26.2; also elsewhere on the board

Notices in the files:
parts and their libraries:
COPYRIGHT: Copyright (C) 2021 Ultra Librarian. All rights reserved.
COPYRIGHT: Copyright (C) 2023 Ultra Librarian. All rights reserved.
